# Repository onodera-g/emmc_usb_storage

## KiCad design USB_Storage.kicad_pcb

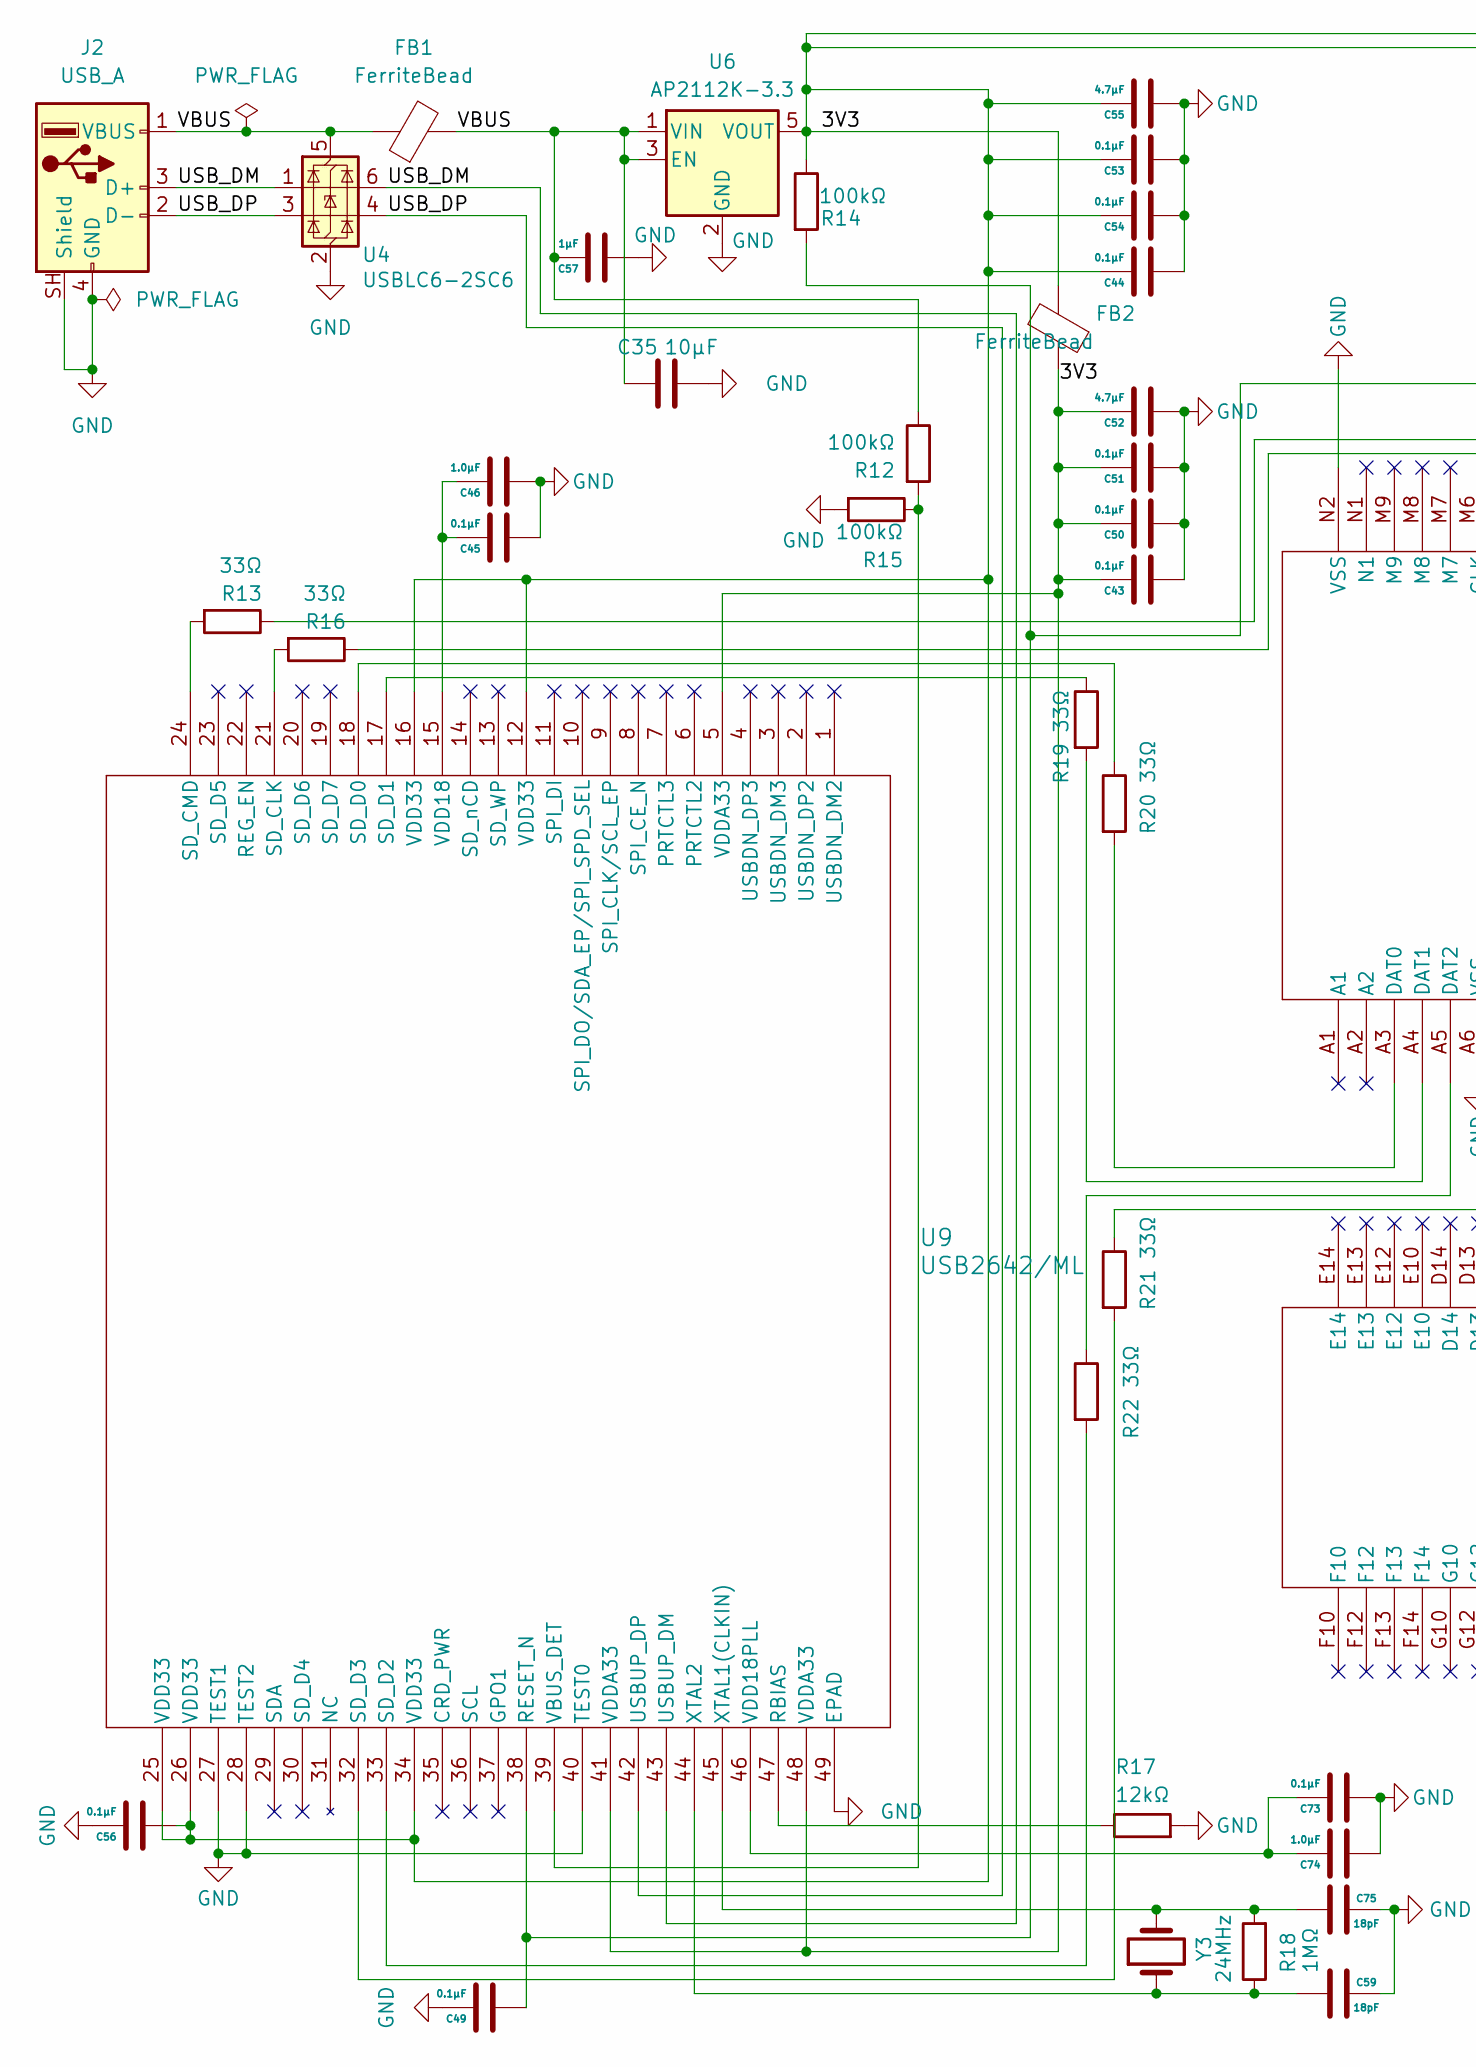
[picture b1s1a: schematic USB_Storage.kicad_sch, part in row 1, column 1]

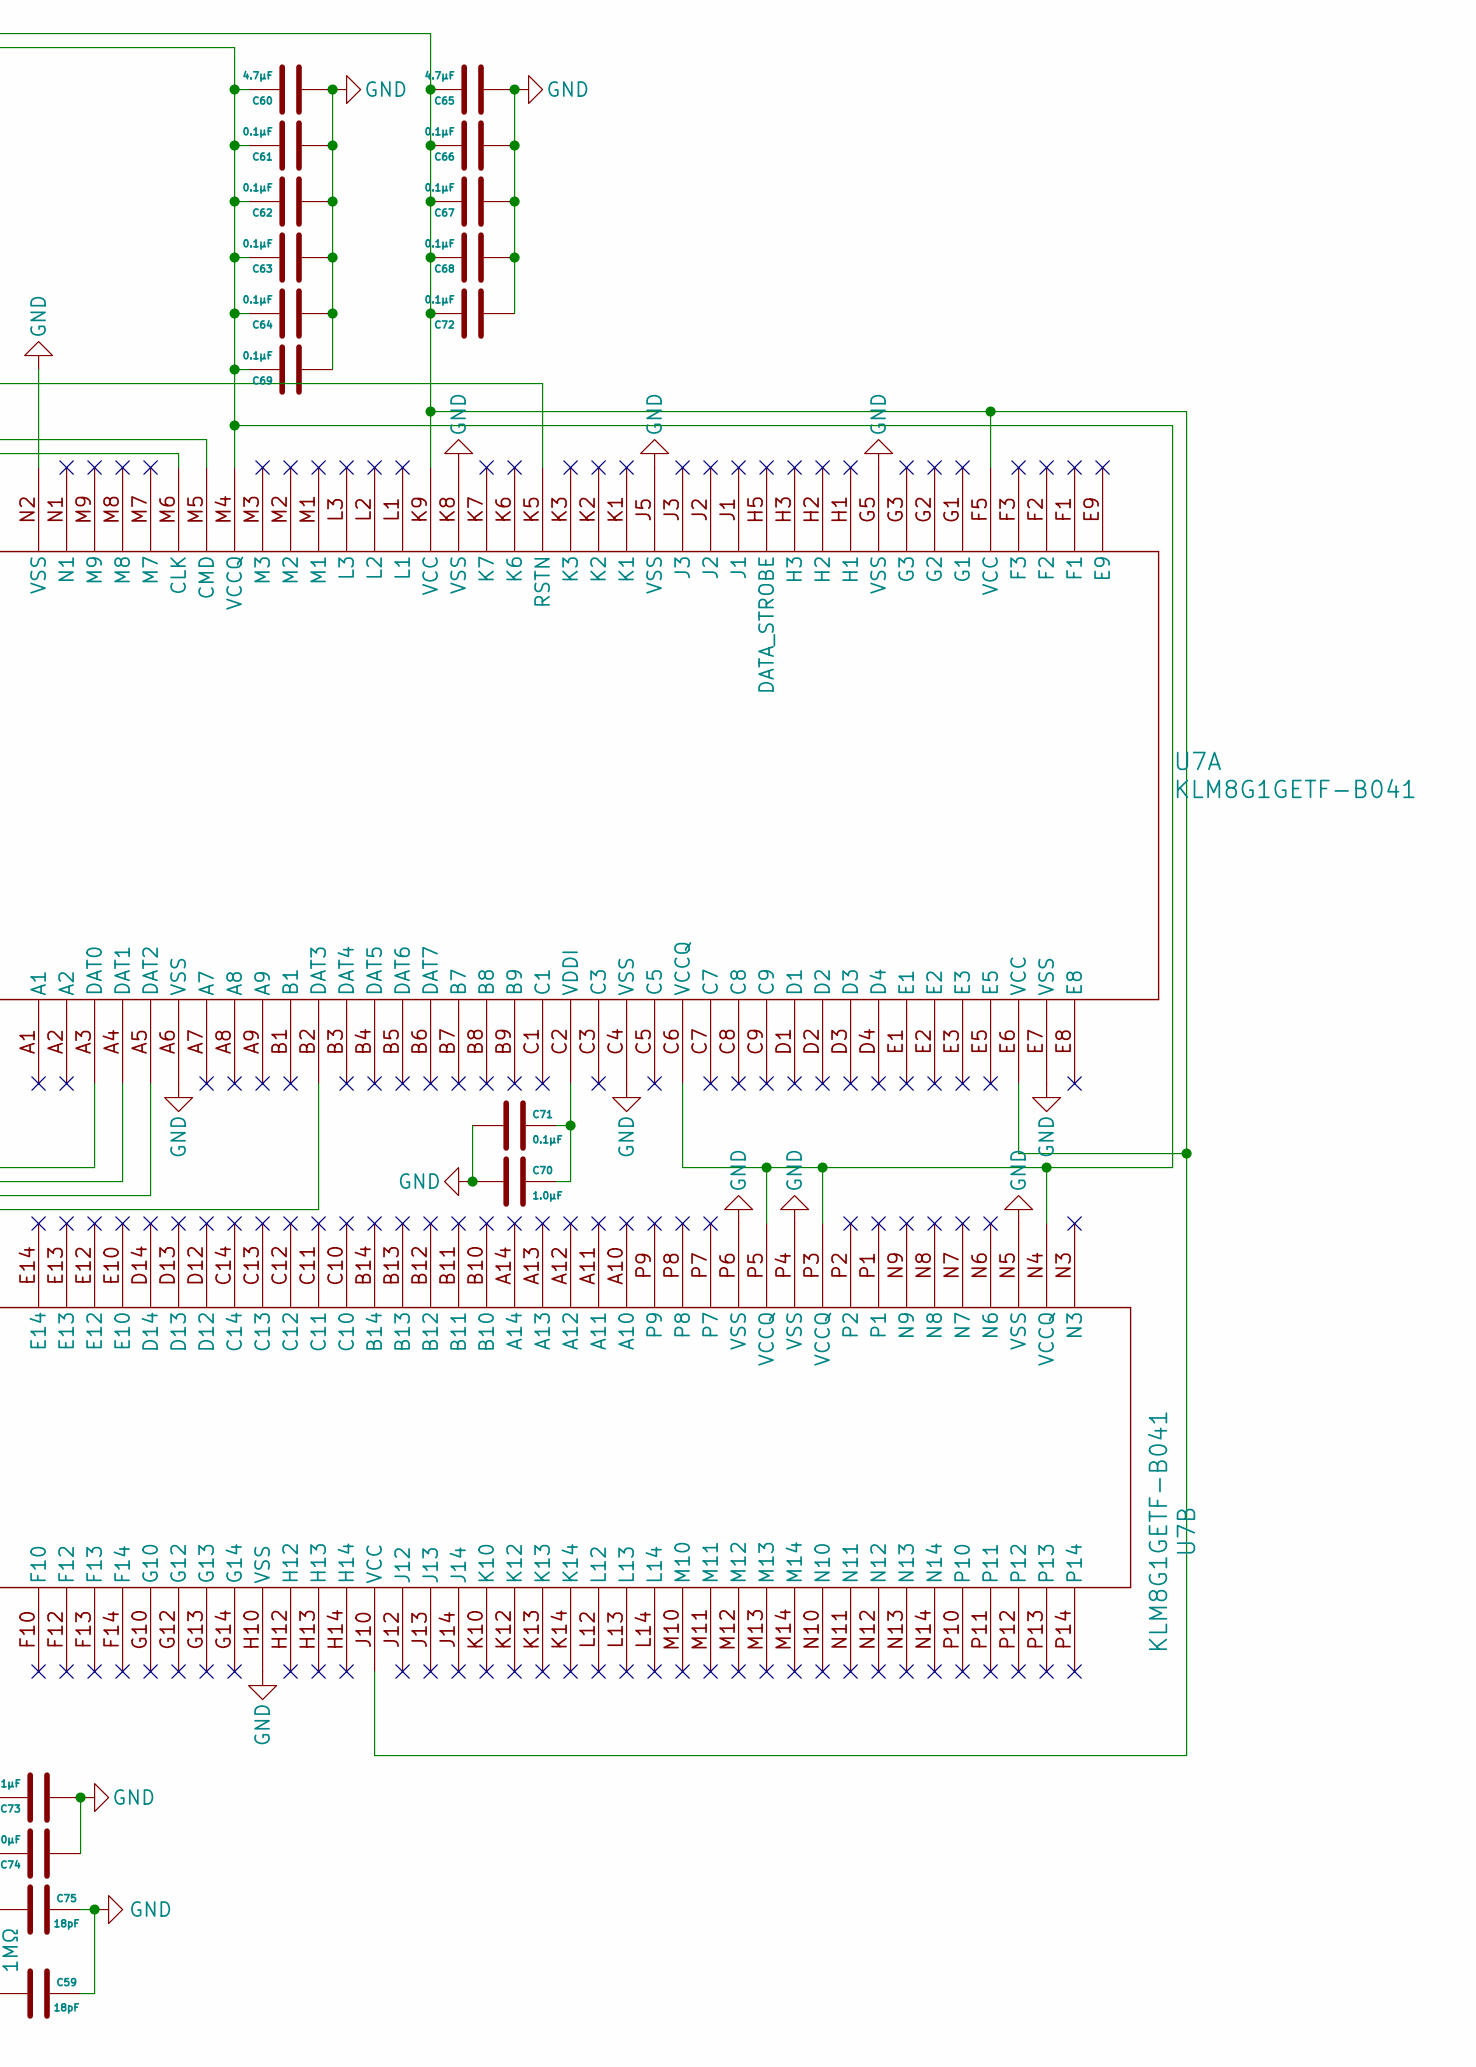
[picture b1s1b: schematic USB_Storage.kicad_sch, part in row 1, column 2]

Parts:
C35: 10µF; C_1206_3216Metric_Pad1.33x1.80mm_HandSolder
C43, C44, C45, C49, C50, C51, C53, C54, C56, C61, C62, C63, C64, C66, C67, C68, C69, C71, C72, C73: 0.1µF; C_1206_3216Metric_Pad1.33x1.80mm_HandSolder
C46, C70, C74: 1.0µF; C_1206_3216Metric_Pad1.33x1.80mm_HandSolder
C52, C55, C60, C65: 4.7µF; C_1206_3216Metric_Pad1.33x1.80mm_HandSolder
C57: 1µF; C_1206_3216Metric_Pad1.33x1.80mm_HandSolder
C59, C75: 18pF; C_1206_3216Metric_Pad1.33x1.80mm_HandSolder
FB1, FB2: FerriteBead; C_1206_3216Metric_Pad1.33x1.80mm_HandSolder
J2: USB_A; USB_A_Molex_67643_Horizontal
R12, R14, R15: 100kΩ; C_1206_3216Metric_Pad1.33x1.80mm_HandSolder
R13, R16, R19, R20, R21, R22: 33Ω; C_1206_3216Metric_Pad1.33x1.80mm_HandSolder
R17: 12kΩ; C_1206_3216Metric_Pad1.33x1.80mm_HandSolder
R18: 1MΩ; C_1206_3216Metric_Pad1.33x1.80mm_HandSolder
U4: USBLC6-2SC6; SOT-23-6
U6: AP2112K-3.3; SOT-23-5
U7: KLM8G1GETF-B041; KLMBG2JENB-B041_SAM
U9: USB2642/ML; QFN48_7X7MC_MCH
Y3: 24MHz; Crystal_SMD_5032-2Pin_5.0x3.2mm_HandSoldering

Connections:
/3V3: C43.1, C44.1, C50.1, C51.1, C52.1, C53.1, C54.1, C55.1, C56.2, C60.1, C61.1, C62.1, C63.1, C64.1, C65.1, C66.1, C67.1, C68.1, C69.1, C72.1, FB2.1, FB2.2, R14.1, U6.5 (VOUT), U7.C6 (VCCQ), U7.E6 (VCC), U7.F5 (VCC), U7.J10 (VCC), U7.K9 (VCC), U7.M4 (VCCQ), U7.N4 (VCCQ), U7.P3 (VCCQ), U7.P5 (VCCQ), U9.5 (VDDA33), U9.12 (VDD33), U9.16 (VDD33), U9.25 (VDD33), U9.26 (VDD33), U9.34 (VDD33), U9.41 (VDDA33), U9.48 (VDDA33)
/USB_DM: J2.3 (D+), U4.1 (I/O1), U4.6 (I/O1), U9.43 (USBUP_DM)
/USB_DP: J2.2 (D-), U4.3 (I/O2), U4.4 (I/O2), U9.42 (USBUP_DP)
/VBUS: C35.2, C57.1, FB1.1, FB1.2, J2.1 (VBUS), R12.1, U4.5 (VBUS), U6.1 (VIN), U6.3 (EN)
GND: C35.1, C43.2, C44.2, C45.2, C46.2, C49.1, C50.2, C51.2, C52.2, C53.2, C54.2, C55.2, C56.1, C57.2, C59.1, C60.2, C61.2, C62.2, C63.2, C64.2, C65.2, C66.2, C67.2, C68.2, C69.2, C70.2, C71.2, C72.2, C73.2, C74.2, C75.1, J2.4 (GND), J2.SH (Shield), R15.2, R17.2, U4.2 (GND), U6.2 (GND), U7.A6 (VSS), U7.C4 (VSS), U7.E7 (VSS), U7.G5 (VSS), U7.H10 (VSS), U7.J5 (VSS), U7.K8 (VSS), U7.N2 (VSS), U7.N5 (VSS), U7.P4 (VSS), U7.P6 (VSS), U9.27 (TEST1), U9.28 (TEST2), U9.40 (TEST0), U9.49 (EPAD)
unnamed: R16.1, U7.M6 (CLK)
unnamed: R13.1, U7.M5 (CMD)
unnamed: R20.2, U7.A3 (DAT0)
unnamed: R19.2, U7.A4 (DAT1)
unnamed: R22.1, U7.A5 (DAT2)
unnamed: R21.1, U7.B2 (DAT3)
unnamed: C49.2, R14.2, U7.K5 (RSTN), U9.38 (RESET_N)
unnamed: C70.1, C71.1, U7.C2 (VDDI)
unnamed: R17.1, U9.47 (RBIAS)
unnamed: R16.2, U9.21 (SD_CLK)
unnamed: R13.2, U9.24 (SD_CMD)
unnamed: R20.1, U9.18 (SD_D0)
unnamed: R19.1, U9.17 (SD_D1)
unnamed: R22.2, U9.33 (SD_D2)
unnamed: R21.2, U9.32 (SD_D3)
unnamed: R12.2, R15.1, U9.39 (VBUS_DET)
unnamed: C45.1, C46.1, U9.15 (VDD18)
unnamed: C73.1, C74.1, U9.46 (VDD18PLL)
unnamed: C75.2, R18.2, U9.45 (XTAL1(CLKIN)), Y3.2
unnamed: C59.2, R18.1, U9.44 (XTAL2), Y3.1

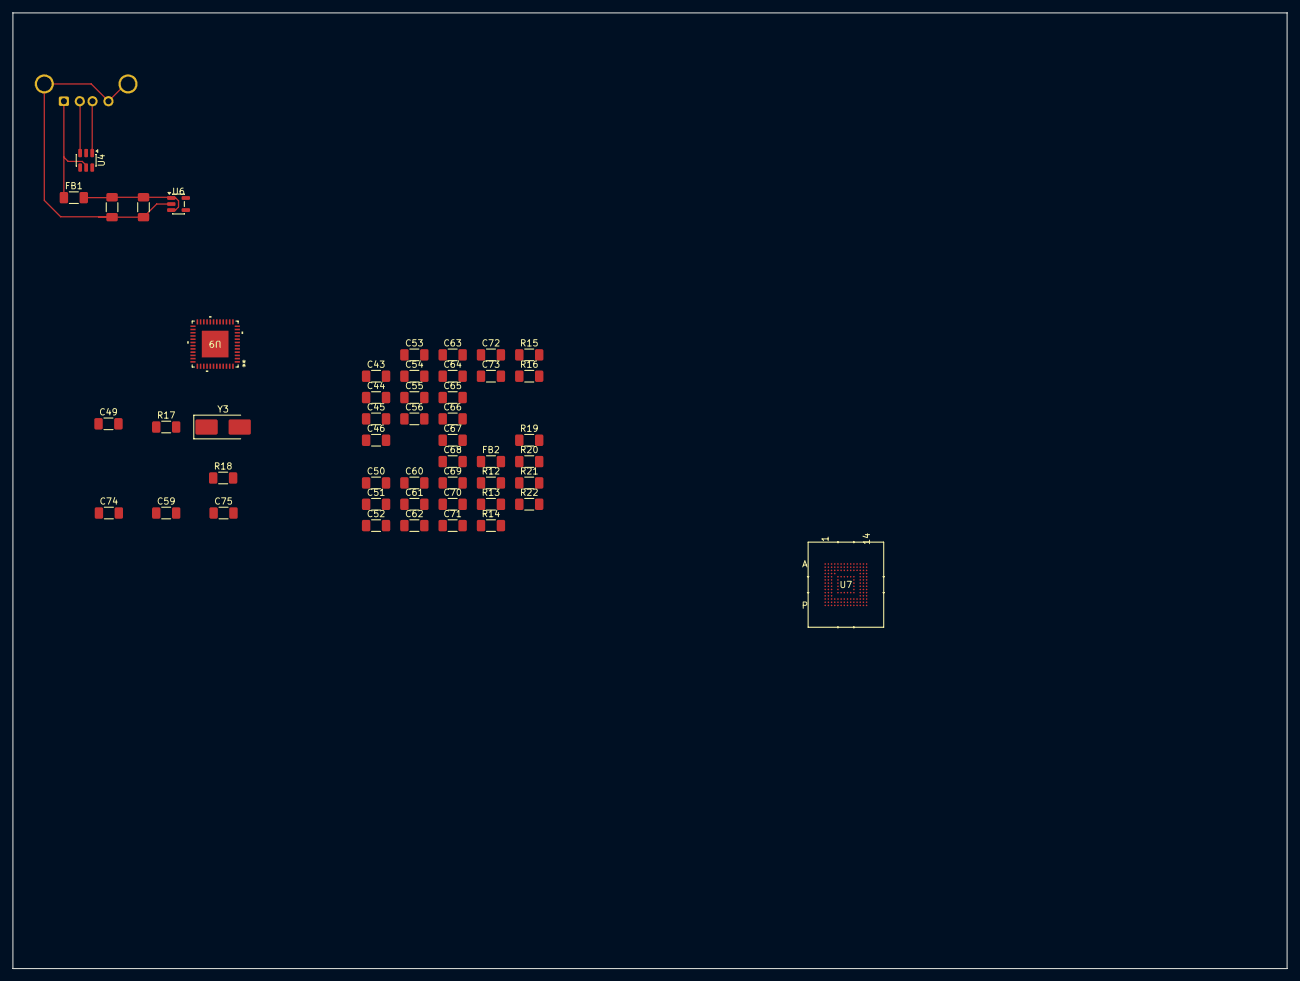
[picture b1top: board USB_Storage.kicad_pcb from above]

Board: 2 copper layers, 200.0 x 150.0 mm, 50 parts (1 on the bottom side), 25 nets.

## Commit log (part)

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2026-05-03 Initial commit: KiCAD USB storage project
2026-05-03 Add .gitignore, remove .history from tracking
2026-05-05 回路図の更新
2026-05-09 回路図の更新をしました
2026-05-17 回路図を更新しました
2026-05-28 ERCのエラーの修正
2026-05-31 バックアップフォルダを削除
2026-06-06 PCBの更新
2026-06-09 PCBレイアウトの更新
